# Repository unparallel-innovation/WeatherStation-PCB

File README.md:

[![CC BY-NC-SA 4.0][cc-by-nc-sa-shield]][cc-by-nc-sa]

This work is licensed under a
[Creative Commons Attribution-NonCommercial-ShareAlike 4.0 International License][cc-by-nc-sa].

[![CC BY-NC-SA 4.0][cc-by-nc-sa-image]][cc-by-nc-sa]

[cc-by-nc-sa]: http://creativecommons.org/licenses/by-nc-sa/4.0/
[cc-by-nc-sa-image]: https://licensebuttons.net/l/by-nc-sa/4.0/88x31.png
[cc-by-nc-sa-shield]: https://img.shields.io/badge/License-CC%20BY--NC--SA%204.0-lightgrey.svg

# Unparallel Weather Station PCB

The Weather Station PCB is a board that together with, Software and 3D case allows anyone to build their low-cost weather station. The Weather Station PCB was made open source, so we are sharing in this repository the custom PCB design (Eagle and Gerbers files) and other information, as the BOM and item lists. The software for the weather station is also open-source and can be used as is, or freely customized to meet your own needs and requirements. A model for printing a 3D case for your weather station is also provided (both in other repositories).  

The Weather Station PCB using low-cost hardware and a LoPy4 board. The LoPy4 board is equipped with several connectivity options (e.g. Sigfox, LoRa, Wi-Fi and Bluetooth). Currently, the weather station uses Sigfox and/or Wi-Fi to send the data to the cloud, however, the software can be extended to support other connectivity options. A Grafana dashboard is then used to display the historical weather data that is stored on the cloud.

The weather station uses an external sensor (AM2315) for reading temperature and relative humidity, a weather meter kit (SEN-15901) for wind speed, wind direction and precipitation. The weather station is powered from a Li-Ion battery that is charged with a photovoltaic panel which is also used to measure solar radiation. Due to the system’s low-power operation and solar energy harvesting features, it is energy autonomous and can be deployed in remote places.

Note: the custom Weather Station PCB may be ordered via [PCBWay shared project link](https://www.pcbway.com/project/shareproject/Unparallel_Weather_Station_PCB.html).

#### Measured parameters:
*	Temperature (ºC)
*	Relative Humidity (%)
*	Rainfall (mm/h)
*	Wind Speed (km/h)
*	Wind Gust Speed (km/h)
*	Wind Direction (degrees)
*	Wind Gust Direction (degrees)
*	Solar Radiation (W/m2)
*	Battery Voltage (V)

#### Components:
*	[LoPy 4.0](https://pycom.io/product/lopy4/)
* [Unparallel WeatherStation PCB](https://www.pcbway.com/project/shareproject/Unparallel_Weather_Station_PCB.html)
*	[Unparallel WeatherStation Enclosure](https://github.com/unparallel-innovation/WeatherStation-Enclosure)
*	[Encased I2C Temperature/Humidity Sensor - AM2315](https://www.adafruit.com/product/1293)
*	[Weather Meter Kit - SEN-15901](https://www.sparkfun.com/products/15901)
*	[Li-Ion battery (3.65V - 8000mAh)](https://www.tme.eu/en/details/cl-18650-29e_1s3p/rechargeable-batteries/cellevia-batteries/)
*	[Solar Panel (2.5W - 116x160mm)](https://www.seeedstudio.com/2-5W-Solar-Panel-116X160.html)
*	[Sigfox Antenna Kit (868MHz)](https://pycom.io/product/lora-868mhz-915mhz-sigfox-antenna-kit/)
* [Expansion Board 3.0](https://pycom.io/product/expansion-board-3-0/)

## Related Repositories:
*	[Unparallel WeatherStation Enclosure](https://github.com/unparallel-innovation/WeatherStation-Enclosure)
*	[Unparallel WeatherStation Documentation](https://github.com/unparallel-innovation/WeatherStation-Documentation)
*	[Unparallel WeatherStation Software](https://github.com/unparallel-innovation/WeatherStation-Software)
*	[Unparallel WeatherStation Connector](https://github.com/unparallel-innovation/WeatherStation-Connector)

###### This work was done in the context of SmartAgriHubs Research Project, which has received funding from the European Union’s Horizon 2020 research and innovation programme under grant agreement No 818182

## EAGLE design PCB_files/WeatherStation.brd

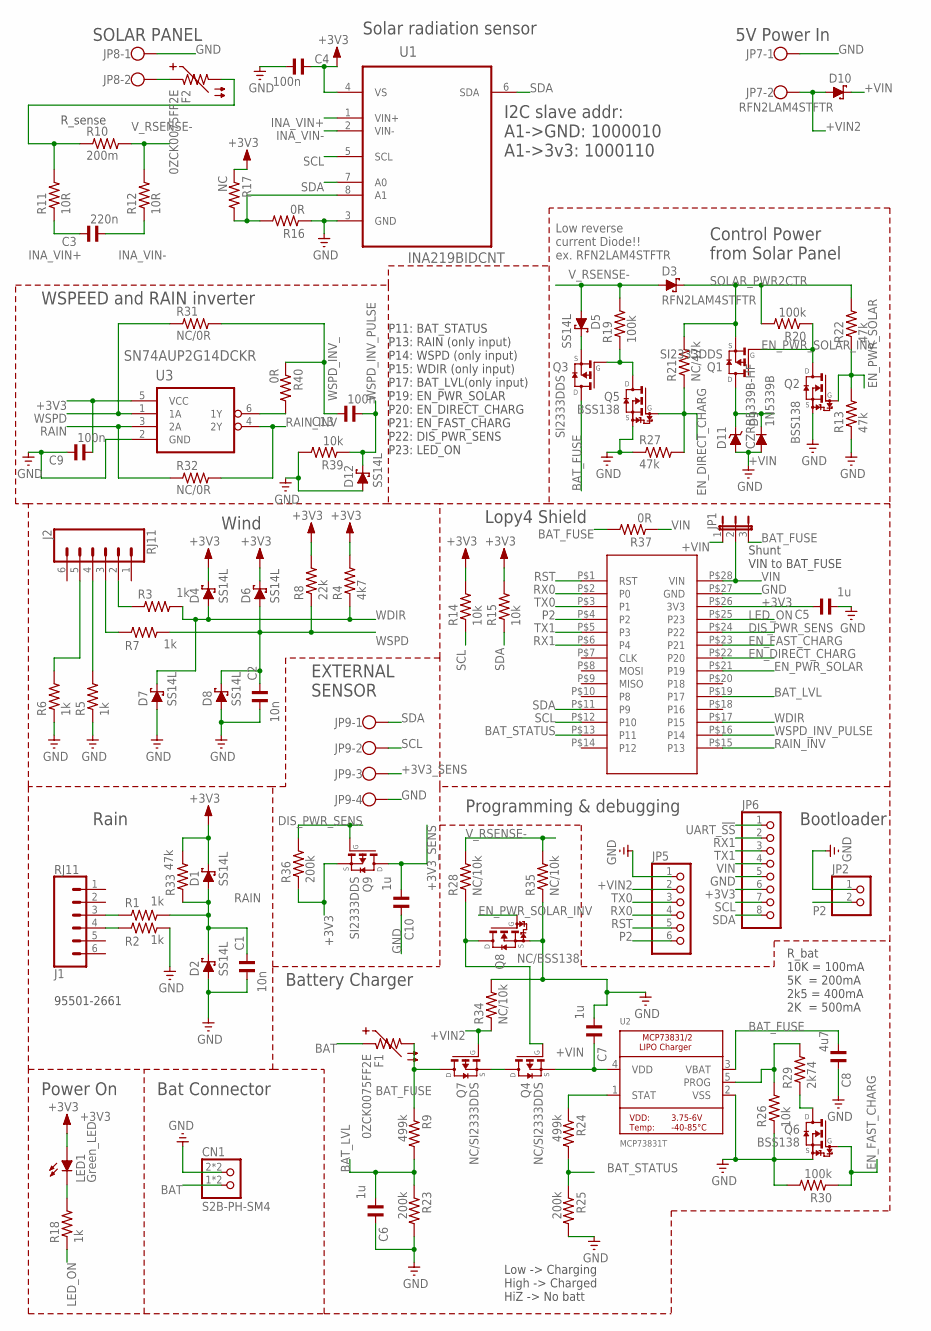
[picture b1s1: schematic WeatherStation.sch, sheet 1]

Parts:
C1, C2: 10n; C0603/C0805_PROTO_SLIM
C3: 220n; C0603
C4, C9, C13: 100n; C0603
C5, C6, C7, C10: 1u; C0603/C0805_PROTO_SLIM
C8: 4u7; C0603/C0805_PROTO_SLIM
CN1: S2B-PH-SM4; JST-PH-2-SMT-RA_OK
D1, D2, D4, D5, D6, D7, D8, D12: SS14L; SUB_SMA_PROTO
D3, D10: RFN2LAM4STFTR; SMA_SOD-128_PROTO
D9: 1N5339B; DO15-12
D11: CZRB5339B-HF; SMB_PROTO
F1, F2: 0ZCK0075FF2E; R0603/R0805_PROTO_SLIM
J1, J2: RJ11; RJ11-6
JP1: JP2E-0805; R0805/2
JP2: PINHD-1X2; 1X02
JP5: PINHD-1X6; 1X06
JP6: PINHD-1X8; 1X08
JP7, JP8: W237-102
JP9: W237-4
LED1: Green_LED; CHIP-LED0805
Q1, Q3, Q9: SI2333DDS; SOT23_PROTO_SLIM
Q2, Q5, Q6: BSS138; SOT23_PROTO_SLIM
Q4, Q7: NC/SI2333DDS; SOT23_PROTO_SLIM
Q8: NC/BSS138; SOT23_PROTO_SLIM
R1, R2, R3, R5, R6, R7, R18: 1k; R0603
R4: 4k7; R0603
R8: 22k; R0603
R9, R24: 499k; R0603/R0805_PROTO_SLIM
R10: 200m; R0603/R0805_PROTO_SLIM
R11, R12: 10R; R0603
R13, R22, R27, R33: 47k; R0603
R14, R15, R26, R39: 10k; R0603
R16, R37, R40: 0R; R0603
R17: NC; R0603
R19, R20, R30: 100k; R0603
R21: NC/47k; R0603
R23, R25, R36: 200k; R0603/R0805_PROTO_SLIM
R28, R34, R35: NC/10k; R0603
R29: 2k74; R0603/R0805_PROTO_SLIM
R31, R32: NC/0R; R0603
U1: INA219BIDCNT; SOT65P280X145-8N
U2: MCP73831T; SOT23-5
U3: SN74AUP2G14DCKR; SOT65P210X110-6N_EDIT
U$2: LOPY4_SHIELD

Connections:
+3V3: C4.1, C5.1, C9.2, D1.C, D4.C, D6.C, JP6.6, LED1.A, Q9.2 (S), R4.2, R8.2, R14.2, R15.2, R17.1, R33.2, R36.1, U1.4 (VS), U3.5 (VCC), U$2.P$26 (3V3); also elsewhere on the board
+3V3_SENS: C10.2, JP9.3, Q9.3 (D)
+VIN: C7.1, D9.C, D10.C, D11.C, JP1.1, Q1.3 (D), Q4.2 (S), U2.4 (VDD)
+VIN2: D10.A, JP5.2, JP7.2, Q7.1 (G), R34.1
BAT: CN1.1 (2), CN1.3 (2), F1.1
BAT_FUSE: C8.2, F1.2, JP1.3, Q3.3 (D), Q7.3 (D), R9.1, R37.2, U2.3 (VBAT)
BAT_LVL: C6.2, R9.2, R23.1, U$2.P$19 (P17)
BAT_STATUS: R24.2, R25.1, U$2.P$13 (P11)
DIS_PWR_SENS: Q9.1 (G), R36.2, U$2.P$24 (P22)
EN_DIRECT_CHARG: Q5.1 (G), R21.1, R27.2, U$2.P$22 (P20)
EN_FAST_CHARG: Q6.1 (G), R30.1, U$2.P$23 (P21)
EN_PWR_SOLAR: Q2.1 (G), R13.2, R22.1, U$2.P$21 (P19)
EN_PWR_SOLAR_INV: Q1.1 (G), Q2.3 (D), Q8.1 (G), R20.1
GND: C1.2, C2.2, C4.2, C5.2, C6.1, C7.2, C8.1, C9.1, C10.1, CN1.2 (1), CN1.4 (1), D2.A, D7.A, D8.A, D9.A, D11.A, D12.A, JP2.1, JP5.1, JP6.5, JP7.1, JP8.1, JP9.4, Q2.2 (S), Q5.2 (S), Q6.2 (S), Q8.2 (S), R2.2, R5.1, R6.1, R13.1, R16.1, R23.2, R25.2, R26.1, R27.1, R30.2, R34.2, R35.1, R39.2, U1.3 (GND), U2.2 (VSS), U3.2 (GND), U$2.P$27 (GND); also elsewhere on the board
INA_VIN+: C3.1, R11.1, U1.1 (VIN+)
INA_VIN-: C3.2, R12.1, U1.2 (VIN-)
LED_ON: R18.1, U$2.P$25 (P23)
unnamed: D5.C, Q3.2 (S)
unnamed: F2.1, JP8.2
unnamed: J1.4, R2.1
unnamed: J1.3, R1.1
unnamed: J2.2, R3.1
unnamed: J2.3, R7.1
unnamed: J2.4, R5.2
unnamed: J2.5, R6.2
unnamed: Q4.1 (G), Q8.3 (D), R28.1
unnamed: R26.2, R29.2, U2.5 (PROG)
unnamed: R16.2, R17.2, U1.8 (A1)
unnamed: LED1.C, R18.2
unnamed: Q6.3 (D), R29.1
unnamed: R40.2, U3.6 (1Y)
unnamed: Q3.1 (G), Q5.3 (D), R19.1
unnamed: R24.1, U2.1 (STAT)
unnamed: Q4.3 (D), Q7.2 (S)
P2: JP2.2, JP5.6, U$2.P$4 (P2)
RAIN: C1.1, D1.A, D2.C, R1.2, R32.1, R33.1, U3.3 (2A)
RAIN_INV: R32.2, U3.4 (2Y), U$2.P$15 (P13); also elsewhere on the board
RST: JP5.5, U$2.P$1 (RST); also elsewhere on the board
RX0: JP5.4, U$2.P$2 (P0)
RX1: JP6.2, U$2.P$6 (P4); also elsewhere on the board
SCL: JP6.7, JP9.2, R14.1, U1.5 (SCL), U$2.P$12 (P10); also elsewhere on the board
SDA: JP6.8, JP9.1, R15.1, U1.6 (SDA), U1.7 (A0), U$2.P$11 (P9); also elsewhere on the board
SOLAR_PWR2CTR: D3.C, Q1.2 (S), R20.2, R21.2, R22.2
TX0: JP5.3, U$2.P$3 (P1)
TX1: JP6.3, U$2.P$5 (P3); also elsewhere on the board
UART_!SS: JP6.1; also elsewhere on the board
VBUS_SOLAR: F2.2, R10.1, R11.2
VIN: JP1.2, JP6.4, R37.1, U$2.P$28 (VIN)
V_RSENSE-: D3.A, D5.A, R10.2, R12.2, R19.2, R28.2, R35.2
WDIR: D4.A, D7.C, R3.2, R4.1, U$2.P$17 (P15); also elsewhere on the board
WSPD: C2.1, D6.A, D8.C, R7.2, R8.1, R31.1, U3.1 (1A)
WSPD_INV_: C13.1, R31.2, R40.1
WSPD_INV_PULSE: C13.2, D12.C, R39.1, U$2.P$16 (P14); also elsewhere on the board

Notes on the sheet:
Lopy4 Shield
EXTERNAL SENSOR
SOLAR PANEL
Rain
Wind
Solar radiation sensor
I2C slave addr: A1->GND: 1000010 A1->3v3: 1000110
Power On
5V Power In
P11: BAT_STATUS P13: RAIN (only input) P14: WSPD (only input) P15: WDIR (only input) P17: BAT_LVL(only input) P19: EN_PWR_SOLAR P20: EN_DIRECT_CHARG P21: EN_FAST_CHARG P22: DIS_PWR_SENS P23: LED_ON
Programming & debugging
Control Power from Solar Panel
R_bat 10K = 100mA 5K = 200mA 2k5 = 400mA 2K = 500mA
Low -> Charging High -> Charged HiZ -> No batt
Battery Charger
Bootloader
R_sense
95501-2661
Low reverse current Diode!! ex. RFN2LAM4STFTR
WSPEED and RAIN inverter
Bat Connector
Shunt VIN to BAT_FUSE

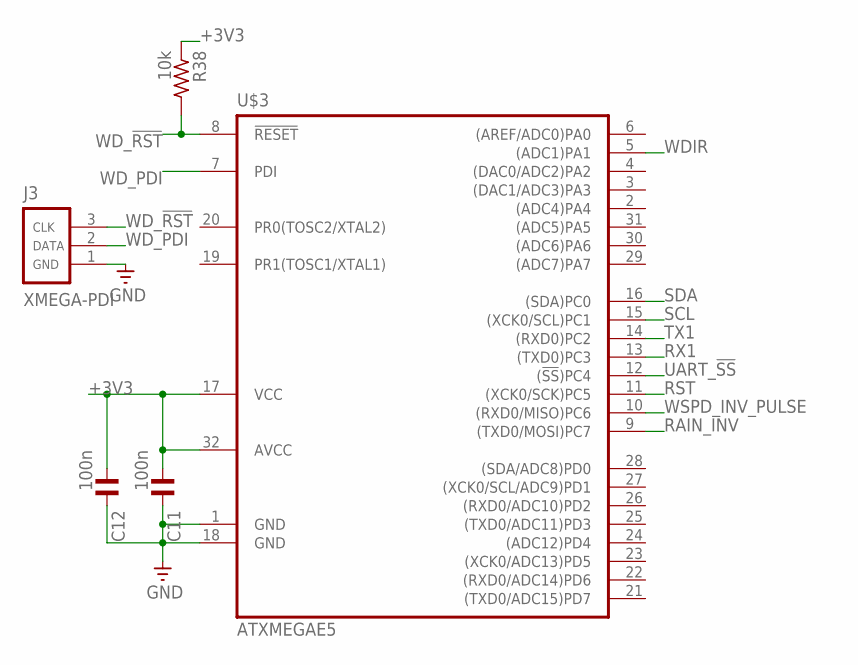
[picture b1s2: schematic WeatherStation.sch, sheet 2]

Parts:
C11, C12: 100n; C0603
J3: XMEGA-PDI; HDR-MA02-3P_P0.05_FABIO
R38: 10k; R0603
U$3: ATXMEGAE5; TQFP32_PROTO_SLIM

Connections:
+3V3: C11.2, C12.2, R38.1, U$3.17 (VCC), U$3.32 (AVCC); also elsewhere on the board
GND: C11.1, C12.1, J3.1, U$3.1 (GND), U$3.18 (GND); also elsewhere on the board
RAIN_INV: U$3.9 ((TXD0/MOSI)PC7); also elsewhere on the board
RST: U$3.11 ((XCK0/SCK)PC5); also elsewhere on the board
RX1: U$3.13 ((TXD0)PC3); also elsewhere on the board
SCL: U$3.15 ((XCK0/SCL)PC1); also elsewhere on the board
SDA: U$3.16 ((SDA)PC0); also elsewhere on the board
TX1: U$3.14 ((RXD0)PC2); also elsewhere on the board
UART_!SS: U$3.12 ((!SS!)PC4); also elsewhere on the board
WDIR: U$3.5 ((ADC1)PA1); also elsewhere on the board
WD_!RST: J3.3, R38.2, U$3.8 (!RESET!)
WD_PDI: J3.2, U$3.7 (PDI)
WSPD_INV_PULSE: U$3.10 ((RXD0/MISO)PC6); also elsewhere on the board

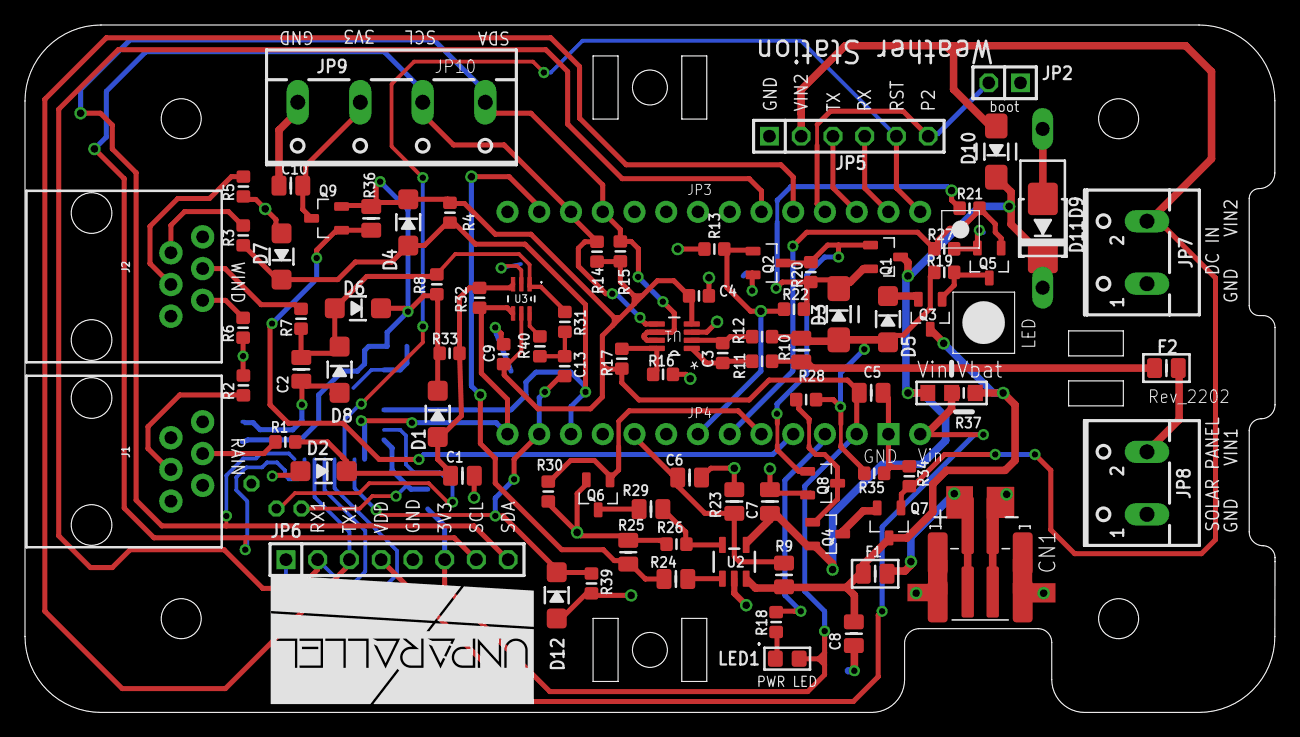
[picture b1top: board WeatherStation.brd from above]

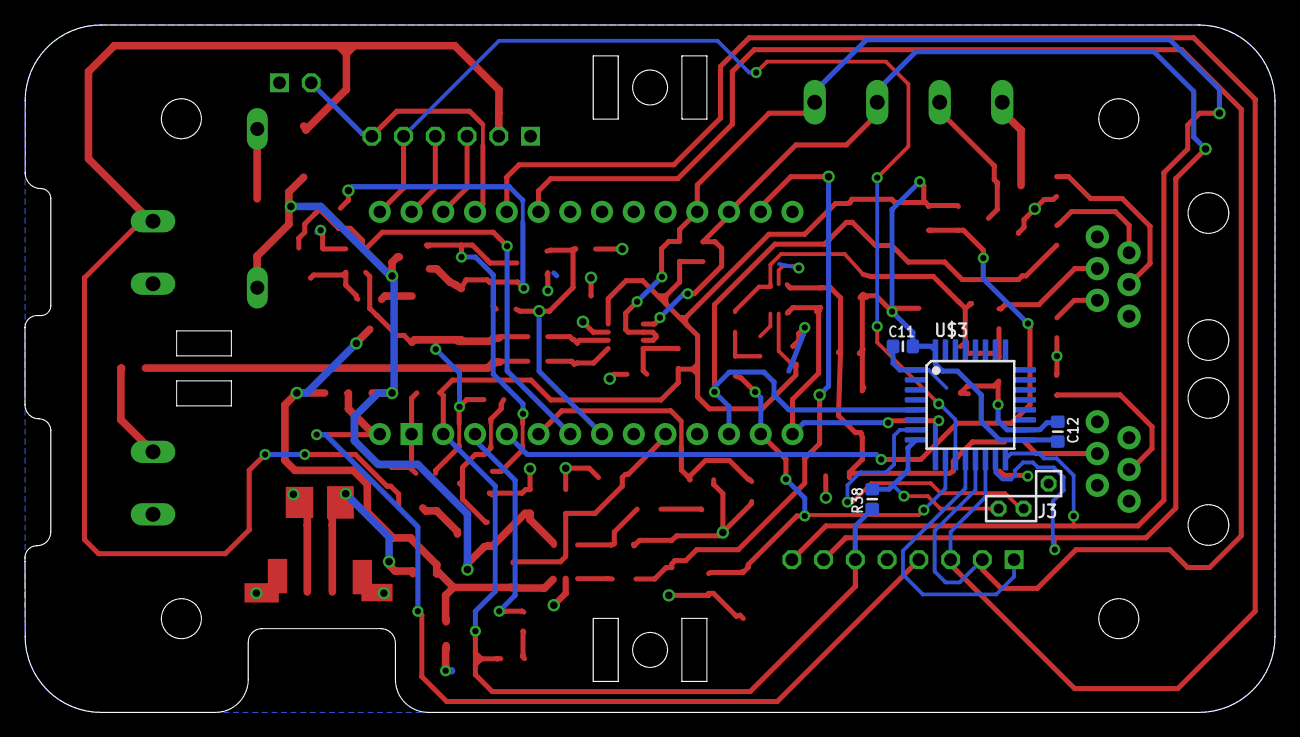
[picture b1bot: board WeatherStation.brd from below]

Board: 2 copper layers, 100.0 x 55.0 mm, 96 parts (5 on the bottom side), 55 nets.

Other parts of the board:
STAND2, STAND3: MOUNTHOLE_110MIL
U$1: UNPARALLEL_LOGO_NEW_0_INVERT_BIG

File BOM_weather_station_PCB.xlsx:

Schematic Reference | Qty per brd | Value | Device | Manufacturer Part Number (MPN) | MFR | Description
C1 C2 | 2 | 10n | C0603 | 885012206089 | Wurth Elektronik | MLCC - SMD/SMT WCAP-CSGP 0.01uF 0603 10% 50V
C3 | 1 | 220n | C0603 | CC0603KRX7R7BB224 | YAGEO | MLCC - SMD/SMT 16V 0.22uF X7R 0603 10%
C4 C9 | 2 | 100n | C0603 | CC0603KRX7R8BB104 | YAGEO | MLCC - SMD/SMT 0603 25V 0.1uF X7R 0603 10%
C5 C6 C7 C10 | 4 | 1u | C0805 | C0805C105K3RACTU | KEMET | MLCC - SMD/SMT 25V 1uF X7R 0805 10%
C8 | 1 | 4u7 | C0805 | GRM21BZ7YA475KE15L | Murata | MLCC - SMD/SMT 35V 4.7uF X7R 0805 10%
CN1 | 1 | S2B-PH-SM4 | JST_2PIN-SMT-RA | S2B-PH-SM4-TB | JST | Male; PH; 2mm; PIN: 2; SMT
D1 D2 D4 D6 D7 D8 D5 | 7 | SS12L | SUB_SMA | SS14L | Taiwan Semiconductor | Schottky Rectifiers Sub SMA-2
D3 D10 | 2 | RFN2LAM4STFTR/SS14L | SOD-128 | RFN2LAM4STFTR | ROHM Semiconductor | Diodes 400V VR 1.5A IO SOD-128; PMDTM
D9 or D11 | 1 | CZRB5339B-HF | DO-214AA-2 OR DO-15-2 | CZRB5339B-HF Or 1N5339B-TP | Comchip Technology Or Micro Commercial Components (MCC) | Zener Diodes ZENER 5W 5.6V SMB DO-214AA-2 Or Zener Diodes 5.0W 5.6V 1uA 865mA 1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
DC_IN SOLAR_POWER | 2 | - | W237-102 | DG300-5.0-2P12 | DEGSON ELECTRONICS | PCB terminal block; angled 90°; 5mm; ways: 2; on PCBs; 2.5mm2; 24A
F1 F2 | 2 | 0ZCK0075FF2E | PTC-0805 | 0ZCK0075FF2E | Bel | Resettable Fuses - PPTC Hold current 750 mA 0805
J1_RAIN J2_WIND | 2 | RJ11 | RJ11-6 | 95501-2661 | Molex | Ethernet Connectors RA 6/6 RJ12 LOW PROFILE THT
JP1 | 1 | CC |  | Soldering Shunt to vbat
JP2 | 1 | - | PINHD-1X2 | DS1023-1*2S21 | CONNFLY | Female; PIN: 2; straight; 2.54mm; THT; 1x2; 3A
LED1 | 1 | - | LED0805 | LG R971-KN-1 | Osram Opto Semiconductor | Standard LEDs - SMD 0805 Green, 570nm 26mcd, 20mA
NCDW-06 | 1 | - | PINHD-1X6 | DS1023-1*6S21 | CONNFLY | Female; PIN: 6; straight; 2.54mm; THT; 1x6; 3A
Q1 Q3 Q9 | 3 | SI2333DDS | SI2333DDS_PROTO | SI2333DDS-T1-GE3 | Vishay | Transistor: P-MOSFET; unipolar; -12V; -5.2A; Idm: -20A; 1.1W; SOT23
Q2 Q5 Q6 | 3 | BSS138 | BSS138 | BSS138-7-F | Diodes Incorporated | MOSFET 300mW 50V DSS SOT-23-3 N-channel
R1 R2 R3 R5 R6 R7 R18 | 7 | 1k | R0603 | CR0603-FX-1001ELF | Bourns | Thick Film Resistors - SMD 0603 1K 1% 1/10W
R10 | 1 | 200m | R0805 | RL1220S-R20-F | Susumu | Current Sense Resistors - SMD 0805 1/3W 0.20ohm 1%
R11 R12 | 2 | 10R | R0603 | CRCW060310R0FKEAC | Vishay | Thick Film Resistors - SMD 0603 1/10Watt 10ohms 1% Commercial Use
R13 R22 R27 R33 | 4 | 47k | R0603 | RC0603FR-0747KL | YAGEO | Thick Film Resistors - SMD 47 kOhms 100mW 0603 1%
R14 R15 R26 | 3 | 10k | R0603 | CR0603-FX-1002ELF | Bourns | Thick Film Resistors - SMD 0603 10K 1% 1/10W
R16 | 1 | CC/10k | R0603 | Soldering Shunt
R19 R20 R30 | 3 | 100k | R0603 | RC0603FR-07100KL | YAGEO | Thick Film Resistors - SMD 0603 100 kOhms 100mW 0603 1%
R23 R25 R36 | 3 | 200k | R0603 | CRCW0603200KFKEAC | Vishay | Thick Film Resistors - SMD 0603 1/10Watt 200Kohms 1%
R29 | 1 | 2k74 | R0603 | RC0603FR-132K74L | YAGEO | Thick Film Resistors - SMD 0603 2.74kOhms 1/10W 0603 1%
R4 | 1 | 4k7 | R0603 | RC0603FR-074K7L | YAGEO | Thick Film Resistors - SMD 4.7 kOhms 100mW 0603 1%
R8 | 1 | 220k | R0603 | RC0603FR-0722KL | YAGEO | Thick Film Resistors - SMD 22 kOhms 100mW 0603 1%
R9 R24 | 2 | 499k | R0603 | CR0603-FX-4993ELF | Bourns | Thick Film Resistors - SMD 499K ohm 0603 1%
SENSOR1 | 2 | - | W237-4 | DG300-5.0-2P12 | DEGSON ELECTRONICS | PCB terminal block; angled 90°; 5mm; ways: 2; on PCBs; 2.5mm2; 24A
U$2 | 2 | LOPY4 pinheader | LOPY4_SHIELD | DS1023-1*14S21 | CONNFLY | Female; PIN: 14; straight; 2.54mm; THT; 1x14; 3A
U1 | 1 | INA219BIDCNT | INA219BIDCNT | INA219BIDCNR | Texas Instruments | Current & Power Monitors & Regulators 0-Drift,Bi-dir Current/Pwr Monitor
U2 | 1 | - | MCP73831/2 | MCP73831T-2ACI/OT | Microchip | Battery Management Charge
U3 | 1 | SN74AUP2G14DCKR | SN74AUP2G14-DCKR | SN74AUP2G14DCKR | Texas Instruments | Inverters Lo-Pwr Dual Schmitt- Trigger Inverter SC70-6

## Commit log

2021-10-07 Update README.md
    Update README.md
2021-10-08 Update README file
2021-10-12 Create LICENSE
2021-10-21 Update the repository structure; Update BOM list; Add/update assembly files; Add link in readme file
2021-10-21 Update README.md
    Update WS pcb image
2021-10-25 Minor changes (license and rainfall word)
2022-05-17 Updated Weather Station files
2022-05-17 Updated WS picture

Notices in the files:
parts and their libraries:
SparkFun-Connectors: Licensing: Creative Commons ShareAlike 4.0 International - https://creativecommons.org/licenses/by-sa/4.0
atmel-xmega_imp: Copyright (C) 20132, Bob Starr
